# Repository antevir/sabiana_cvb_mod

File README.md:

# Sabiana CVB-T Smart Heat Pump Integration Mod

This project modifies the Sabiana CVB-T convector to better integrate with intelligent heat pump systems, such as those from Nibe.

Modern heat pumps optimize energy use by only enabling the heating water supply line when heating is needed. However, the default CVB-T behavior does not detect this. It periodically starts up to check for hot water, regardless of whether any is available — leading to unnecessary fan operation and inefficiency.

## 🔧 Key Features

- **Intelligent Start Logic**  
  Heating only starts when hot water is available, so the unit follows the heat pump instead of waking up to check. This improves efficiency and reduces wear.

- **HMI Touch Interface**  
  A touch panel for monitoring and manual control. It can follow a weekly schedule, with separate settings for active and inactive hours, and an optional fan cycle that runs during active hours to reduce mould.

## 🛠️ Hardware Overview
This project introduces a small custom ESP-based PCB that plugs in between the Sabiana CVB-T main PCB and its front panel (which includes the status LEDs and IR receiver). This board acts as an interceptor and controller, enabling smarter control and communication with a new HMI touch panel over UART.

The interceptor board receives IR commands via the existing CVB-T IR receiver. It also controls the original CVB-T status LEDs and sends commands to the CVB-T using its Modbus interface.

## 📱 Panel

The gear icon opens the time program: week schedule, active settings, inactive settings, and fan cycle. Firmware build instructions are in [sw/README.md](sw/README.md).

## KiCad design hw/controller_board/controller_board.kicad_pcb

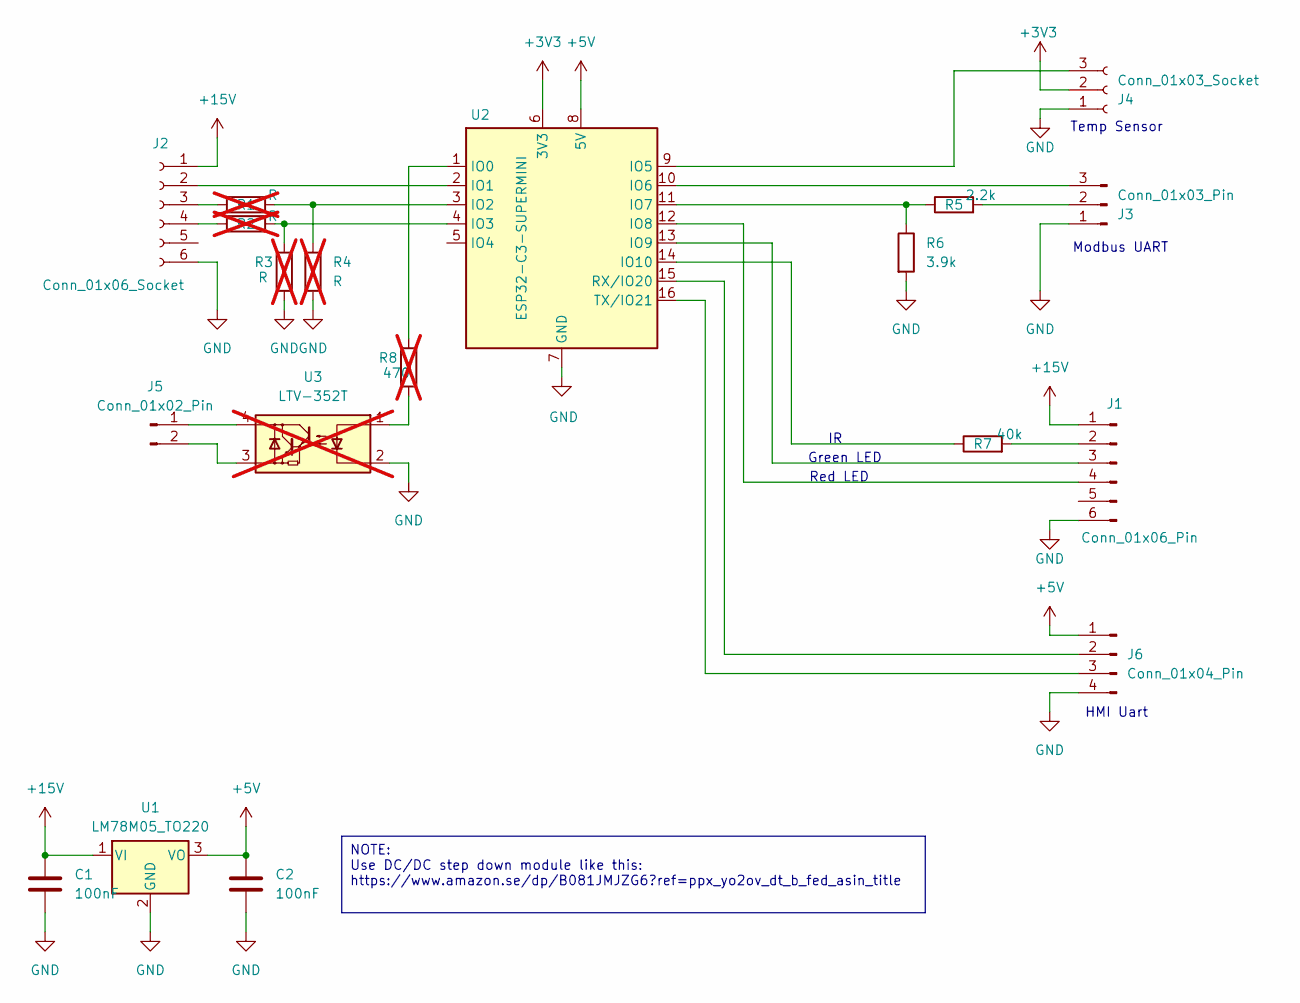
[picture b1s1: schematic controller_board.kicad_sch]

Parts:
C1, C2: 100nF; C_0603_1608Metric_Pad1.08x0.95mm_HandSolder
J1: Conn_01x06_Pin; PinHeader_1x06_P2.54mm_Vertical
J2: Conn_01x06_Socket; PinSocket_1x06_P2.54mm_Horizontal
J3: Conn_01x03_Pin; PinHeader_1x03_P2.54mm_Vertical
J4: Conn_01x03_Socket; PinSocket_1x03_P2.54mm_Vertical
J5: Conn_01x02_Pin; PinHeader_1x02_P2.54mm_Vertical
J6: Conn_01x04_Pin; PinHeader_1x04_P2.54mm_Vertical
R1, R2, R3, R4: R; R_0603_1608Metric_Pad0.98x0.95mm_HandSolder; not fitted
R5: 2.2k; R_0603_1608Metric_Pad0.98x0.95mm_HandSolder
R6: 3.9k; R_0603_1608Metric_Pad0.98x0.95mm_HandSolder
R7: 40k; R_0603_1608Metric_Pad0.98x0.95mm_HandSolder
R8: 470; R_0603_1608Metric_Pad0.98x0.95mm_HandSolder; not fitted
U1: LM78M05_TO220; TO-220-3_Vertical
U2: ESP32-C3-SUPERMINI; esp32_c3_supermini2
U3: LTV-352T; SO-4_4.4x3.6mm_P2.54mm; not fitted

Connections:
+3V3: J4.2, U2.6 (3V3)
+5V: C2.1, J6.1, U1.3 (VO), U2.8 (5V)
+15V: C1.1, J1.1, J2.1, U1.1 (VI)
GND: C1.2, C2.2, J1.6, J2.6, J3.1, J4.1, J6.4, R3.2, R4.2, R6.2, U1.2 (GND), U2.7 (GND), U3.2
unnamed: J1.2, R7.2
unnamed: J1.3, U2.13 (IO9)
unnamed: J1.4, U2.12 (IO8)
unnamed: J2.2, U2.2 (IO1)
unnamed: J2.3, R1.1
unnamed: J2.4, R2.1
unnamed: J3.2, R5.2
unnamed: J3.3, U2.10 (IO6)
unnamed: J4.3, U2.9 (IO5)
unnamed: J5.1, U3.4
unnamed: J5.2, U3.3
unnamed: J6.2, U2.15 (RX/IO20)
unnamed: J6.3, U2.16 (TX/IO21)
unnamed: R8.2, U3.1
unnamed: R8.1, U2.1 (IO0)
unnamed: R1.2, R4.1, U2.3 (IO2)
unnamed: R2.2, R3.1, U2.4 (IO3)
unnamed: R5.1, R6.1, U2.11 (IO7)
unnamed: R7.1, U2.14 (IO10)

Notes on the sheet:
NOTE: Use DC/DC step down module like this: https://www.amazon.se/dp/B081JMJZG6?ref=ppx_yo2ov_dt_b_fed_asin_title
HMI Uart
Temp Sensor
Red LED
Modbus UART
Green LED

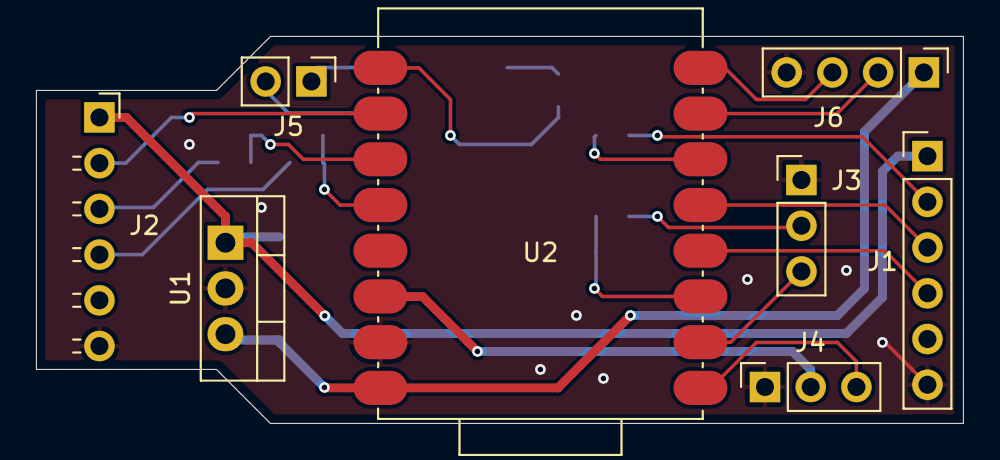
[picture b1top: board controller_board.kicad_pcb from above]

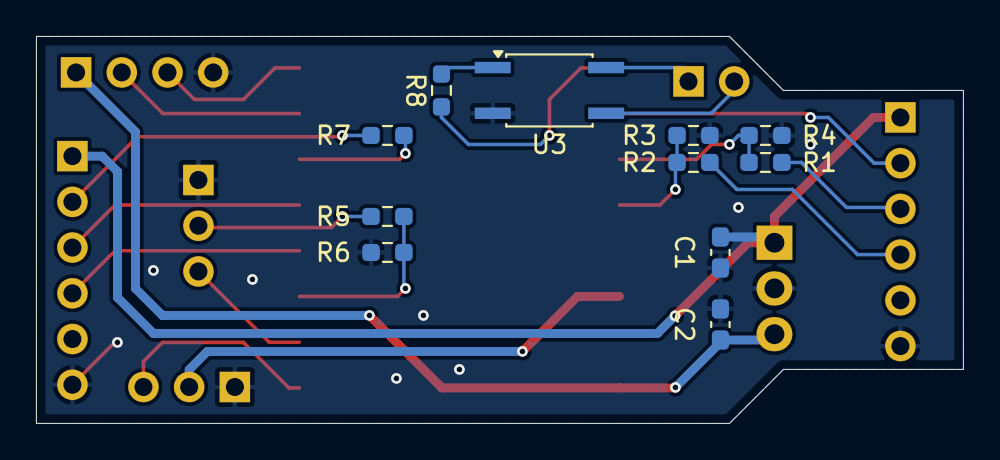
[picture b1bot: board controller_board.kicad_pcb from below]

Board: 2 copper layers, 51.5 x 21.5 mm, 19 parts (11 on the bottom side), 23 nets.

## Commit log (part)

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2025-05-24 Add controller board schematics & PCB
2025-05-24 Add README.md
2025-05-24 Move all source code to sw/
2025-11-03 Switch to SHT3x temp sensor
2025-11-03 Use custom partition table to free up mem
2025-11-03 Power optimizations
    Try to lower the power so that we don't affect the temp sensor too much
2025-11-03 Add heat dissipation comp for air temp
2025-11-03 OTA config
2025-11-10 IR fixes
2025-11-22 Fix IR Off command
2025-11-22 Fix modbus protocol
2025-11-22 controller: Minor power optimizations
2025-11-22 controller: Fix heating
2025-11-30 Add time program UI
2025-11-30 Add logic needed for time programs
